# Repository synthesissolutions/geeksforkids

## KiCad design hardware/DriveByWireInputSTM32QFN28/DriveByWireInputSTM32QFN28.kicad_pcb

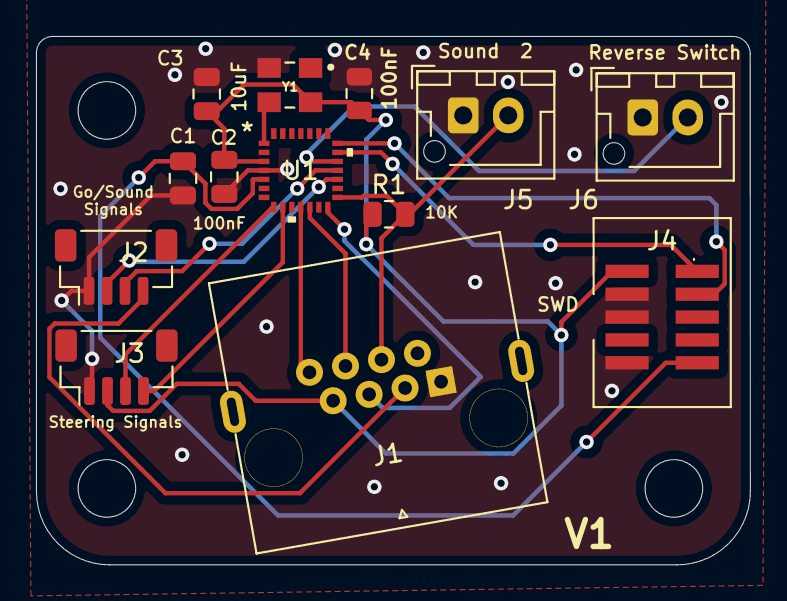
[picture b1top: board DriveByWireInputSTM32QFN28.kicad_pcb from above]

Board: 2 copper layers, 39.7 x 29.4 mm, 16 parts (0 on the bottom side), 16 nets.

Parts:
C1, C2, C4: 100nF; C_0805_2012Metric
C3: 10uF; C_0805_2012Metric
H1, H2, H3: MountingHole; MountingHole_3.2mm_M3
J1: 8P8C; RJ45_x08_Tab_Up
J2, J3: Conn_01x04_Male; JST_SH_BM04B-SRSS-TB_1x04-1MP_P1.00mm_Vertical
J4: Conn_ARM_JTAG_SWD_10; JTAG_SWD_SMD
J5, J6: Conn_01x02_Male; JST_XH_B2B-XH-AM_1x02_P2.50mm_Vertical
R1: 10K; R_0805_2012Metric
U1: STM32G031F4Px; STM32G031G8U6
Y1: ECS-3225MVQ-160-BP-TR; OSC_ECS-3225MVQ-160-BP-TR

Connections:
+3V3: C2.1, C3.1, C4.2, J1.7, J3.2, J4.1 (VTref), R1.1, U1.3 (VDD), Y1.4 (VDD)
/RESET: C1.1, J4.10 (~RESET), U1.5 (PF2-NRST)
AltReverseSwitch: J2.3, U1.18 (PA11PA9)
DriveButton: J2.2, U1.17 (PC6)
GND: C1.2, C2.2, C3.2, C4.1, J1.1, J2.1, J3.1, J4.3 (GND), J4.5 (GND), J4.9 (GNDDetect), J5.1, J6.1, U1.4 (VSS), Y1.2 (GND)
JoyX: J1.5, U1.14 (PB0)
JoyY: J1.6, U1.12 (PA6)
OscillatorIn: U1.1 (PC14-OSC32_IN), Y1.3 (OUTPUT)
Other: J1.8, U1.11 (PA5)
ReverseSwitch: J6.2, U1.19 (PA12PA10)
SWCLK: J4.4 (SWDCLK/TCK), U1.21 (PA14-BOOT0)
SWDIO: J4.2 (SWDIO/TMS), U1.20 (PA13)
SensorCos: J3.4, U1.9 (PA3)
SensorSin: J3.3, U1.8 (PA2)
Sound1: J1.3, J2.4
Sound2: J1.4, J5.2, R1.2, U1.15 (PB1)

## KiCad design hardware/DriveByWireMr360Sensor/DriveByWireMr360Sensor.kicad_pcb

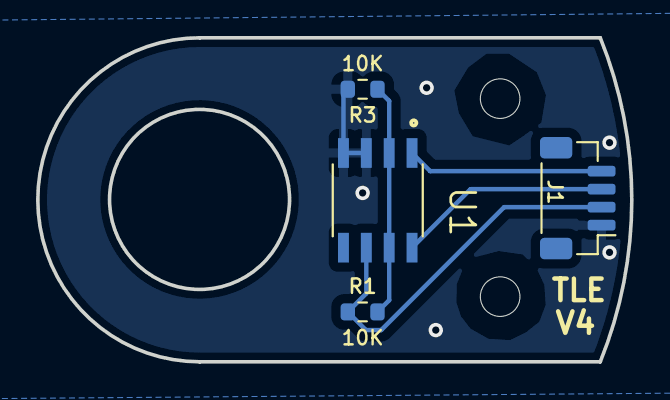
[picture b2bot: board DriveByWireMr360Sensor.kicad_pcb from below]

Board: 2 copper layers, 33.0 x 18.0 mm, 6 parts (4 on the bottom side), 5 nets.

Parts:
H1, H2: MountingHole; MountingHole_2.2mm_M2
J1: Conn_01x04_Male; JST_SH_BM04B-SRSS-TB_1x04-1MP_P1.00mm_Vertical
R1, R3: 10K; R_0603_1608Metric
U1: TLE5501E0001XUMA1; SOIC127P600X175-8N

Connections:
+3V3: J1.2, R1.1, U1.6 (VDD)
AnalogSignal1: J1.3, U1.8 (SIN_P)
AnalogSignal2: J1.4, U1.1 (COS_P)
GND: J1.1, R3.2, U1.3 (GND2), U1.4 (GND1)
unnamed: R1.2, R3.1, U1.2 (COS_N), U1.7 (SIN_N)

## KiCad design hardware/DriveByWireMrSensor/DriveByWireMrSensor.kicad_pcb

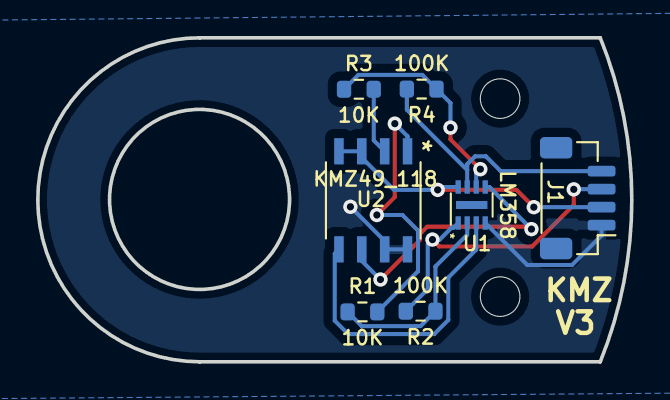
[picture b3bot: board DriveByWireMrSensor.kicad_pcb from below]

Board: 2 copper layers, 33.0 x 18.0 mm, 9 parts (7 on the bottom side), 10 nets.

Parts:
H1, H2: MountingHole; MountingHole_2.2mm_M2
J1: Conn_01x04_Male; JST_SH_BM04B-SRSS-TB_1x04-1MP_P1.00mm_Vertical
R1, R3: 10K; R_0603_1608Metric
R2, R4: 100K; R_0603_1608Metric
U1: LM358; DFN-8-LM358
U2: KMZ49_118

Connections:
+3V3: J1.2, U1.8 (V+), U2.3 (VCC2), U2.4 (VCC1)
AnalogSignal1: J1.3, R2.2, U1.1
AnalogSignal2: J1.4, R4.2, U1.7
GND: J1.1, U1.4 (V-), U2.7 (GND2), U2.8 (GND1)
LM358_InM1: R1.1, R2.1, U1.2 (-)
LM358_InM2: R3.1, R4.1, U1.6 (-)
LM358_InP1: U1.3 (+), U2.5 (OP1)
LM358_InP2: U1.5 (+), U2.6 (OP2)
SourceSignal1: R1.2, U2.1 (ON1)
SourceSignal2: R3.2, U2.2 (ON2)

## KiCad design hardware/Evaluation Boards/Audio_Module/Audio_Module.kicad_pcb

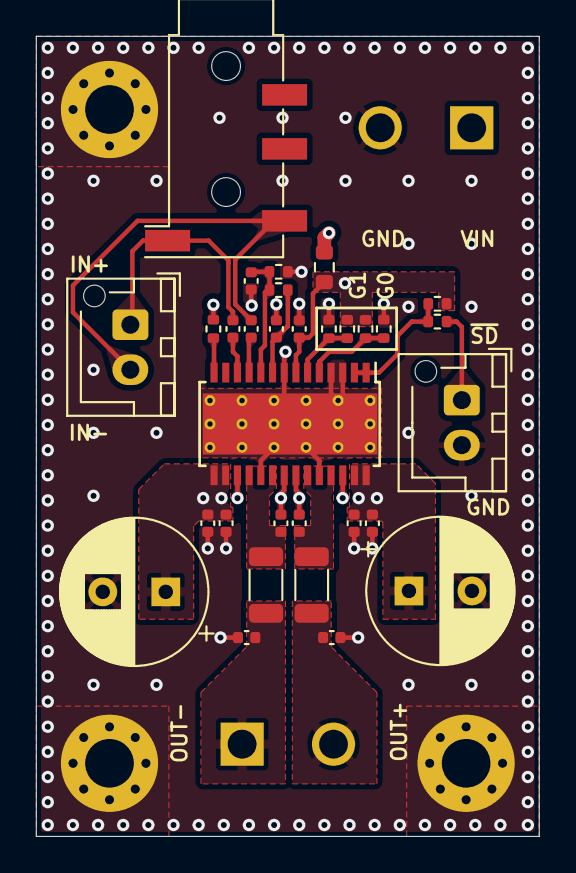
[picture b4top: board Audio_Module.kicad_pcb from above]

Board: 4 copper layers, 27.9 x 44.5 mm, 36 parts (0 on the bottom side), 20 nets.

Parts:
C1, C5: 100uF; CP_Radial_D8.0mm_P3.50mm
C2, C6: 100nF; C_0402_1005Metric
C3, C7, C9, C10: 1nF; C_0402_1005Metric
C4, C14, C15: 1uF; C_0402_1005Metric
C8, C13: 0.47uF; C_0402_1005Metric
C11, C12: 0.68uF; C_0402_1005Metric
FB1, FB2: 120Ohm@100MHz; L_1206_3216Metric
H1, H2, H3: M2.5; MountingHole_2.7mm_M2.5_Pad_Via
J1, J4: 5.08mm; CUI_TB004-508-02BE
J2, J5: 2.54mm; JST_XH_B2B-XH-AM_1x02_P2.50mm_Vertical
J3: 3.5mm; Jack_3.5mm_KoreanHropartsElec_PJ-320D-4A_Horizontal
R1: 10R; R_0603_1608Metric
R2, R3, R4, R5, R10: 100k; R_0402_1005Metric
R6: 1k; R_0402_1005Metric
R7, R8, R9: 0; R_0402_1005Metric
U1: TPA3110D2; HTSSOP-28-1EP_4.4x9.7mm_P0.65mm_EP3.4x9.5mm_Mask2.4x6.17mm_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

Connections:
+12V: C1.1, C2.1, C3.1, C5.1, C6.1, C7.1, J4.1, R1.1, U1.15 (PVCCR), U1.16 (PVCCR), U1.27 (PVCCL), U1.28 (PVCCL)
+12VA: C4.1, R1.2, R2.1, R3.1, R4.1, R5.1, U1.7 (AVCC)
/AUDIO_IN_1_N: C12.1, U1.11 (RINN)
/AUDIO_IN_1_P: C11.2, U1.12 (RINP)
/AUDIO_OUT_FILT_N: C10.2, FB2.2, J1.1
/AUDIO_OUT_FILT_P: C9.1, FB1.2, J1.2
/AUDIO_OUT_N: C13.1, FB2.1, U1.18 (OUTPR), U1.20 (OUTNR)
/AUDIO_OUT_P: C8.1, FB1.1, U1.23 (OUTNL), U1.25 (OUTPL)
/BSN: C13.2, U1.17 (BSPR), U1.21 (BSNR)
/BSP: C8.2, U1.22 (BSNL), U1.26 (BSPL)
/GAIN0: R4.2, R7.1, U1.5 (GAIN0)
/GAIN1: R5.2, R8.1, U1.6 (GAIN1)
/GVDD: C14.1, R9.1, U1.9 (GVDD)
/PBTL: R2.2, U1.14 (PBTL)
/PLIMIT: C15.1, R9.2, R10.1, U1.10 (PLIMIT)
/~SD_2: R3.2, R6.2, U1.1 (~SD), U1.2 (~FAULT)
AUDIO_IN_N: C12.2, J2.2, J3.T
AUDIO_IN_P: C11.1, J2.1, J3.S
GND: C1.2, C2.2, C3.2, C4.2, C5.2, C6.2, C7.2, C9.2, C10.1, C14.2, C15.2, H1.1, H2.1, H3.1, J4.2, J5.2, R7.2, R8.2, R10.2, U1.3 (LINP), U1.4 (LINN), U1.8 (AGND), U1.19 (PGND), U1.24 (PGND), U1.29 (GND)
~SD: J5.1, R6.1

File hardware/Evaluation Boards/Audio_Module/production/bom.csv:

Designator,Footprint,Quantity,Value,LCSC Part #
"C1, C5",CP_Radial_D8.0mm_P3.50mm,2,100uF,C112510
"C10, C3, C7, C9",0402,4,1nF,C106205
"C11, C12",0402,2,0.68uF,C113784
"C13, C8",0402,2,0.47uF,C437527
"C14, C15, C4",0402,3,1uF,C1518208
"C2, C6",0402,2,100nF,C105882
"FB1, FB2",1206,2,120Ohm@100MHz,C3011219
"J2, J5",JST_XH_B2B-XH-AM_1x02_P2.50mm_Vertical,2,2.54mm,C158012
J3,Jack_3.5mm_KoreanHropartsElec_PJ-320D-4A_Horizontal,1,3.5mm,C431535
R1,0603,1,10R,C22859
"R10, R2, R3, R4, R5",0402,5,100k,C60491
R6,0402,1,1k,C11702
"R7, R8, R9",0402,3,0,C17168
U1,HTSSOP-28-1EP_4.4x9.7mm_P0.65mm_EP3.4x9.5mm_Mask2.4x6.17mm_ThermalVias,1,TPA3110D2,C30132

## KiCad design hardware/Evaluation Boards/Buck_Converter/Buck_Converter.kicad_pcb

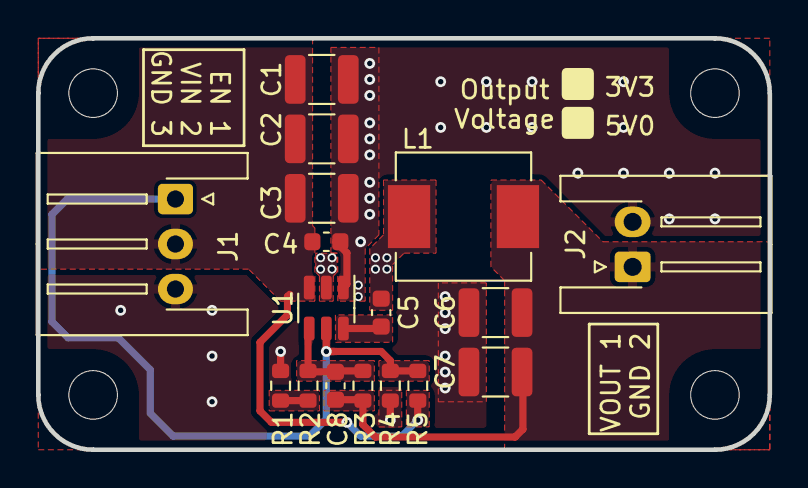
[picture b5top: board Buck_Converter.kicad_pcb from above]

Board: 2 copper layers, 40.6 x 22.9 mm, 21 parts (0 on the bottom side), 8 nets.

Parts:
C1, C2, C3: 10µF; C_1210_3225Metric
C4, C5: 0.1µF; C_0603_1608Metric
C6, C7: 47µF; C_1210_3225Metric
C8: 150pF; C_0603_1608Metric
H1, H2, H3, H4: M2.5; MountingHole_2.7mm_M2.5_ISO14580
J1: Conn_01x03; JST_XH_S3B-XH-A-1_1x03_P2.50mm_Horizontal
J2: Conn_01x02; JST_XH_S2B-XH-A-1_1x02_P2.50mm_Horizontal
L1: 10µH; L_Sunlord_MWSA0603S
R1: 240Ω 1%; R_0603_1608Metric
R2: 13.3kΩ 1%; R_0603_1608Metric
R3: 100kΩ 1%; R_0603_1608Metric
R4: 105kΩ 1%; R_0603_1608Metric
R5: 511kΩ 1%; R_0603_1608Metric
U1: TPS54302; SOT-23-6

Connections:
+5V: C6.1, C7.1, C8.1, J2.1, L1.2, R3.1
+12V: C1.1, C2.1, C3.1, C4.1, J1.2, R5.1, U1.3 (VIN)
/BOOT: C5.1, U1.6 (BOOT)
/EN: J1.1, R4.1, R5.2, U1.5 (EN)
/FB: C8.2, R2.1, R3.2, U1.4 (FB)
/SW: C5.2, L1.1, U1.2 (SW)
GND: C1.2, C2.2, C3.2, C4.2, C6.2, C7.2, J1.3, J2.2, R1.2, R4.2, U1.1 (GND)
unnamed: R1.1, R2.2

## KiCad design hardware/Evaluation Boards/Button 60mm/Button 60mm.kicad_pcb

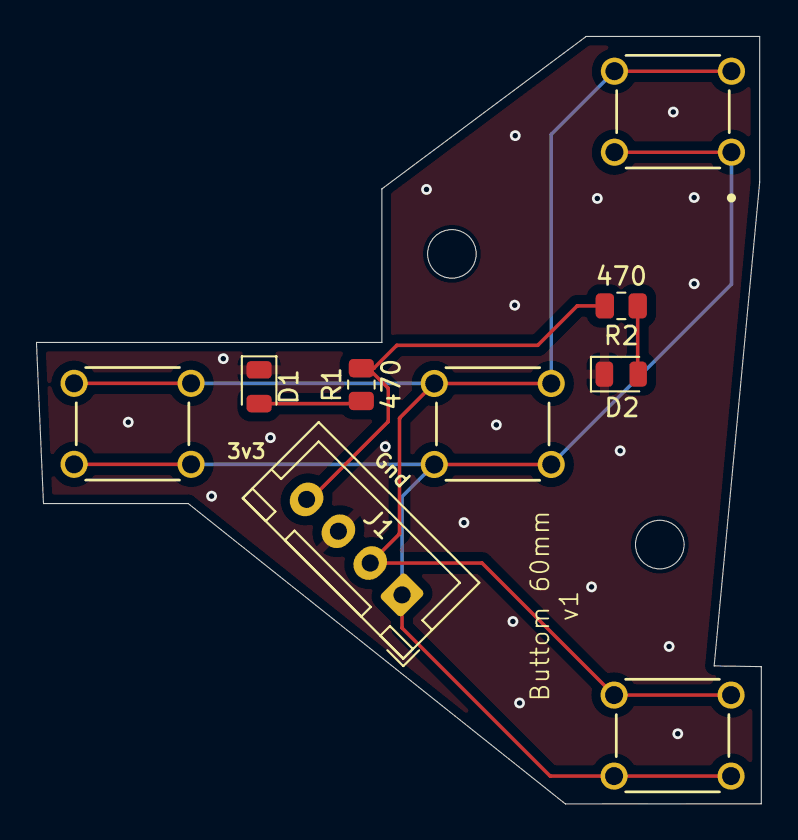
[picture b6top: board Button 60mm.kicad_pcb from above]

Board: 2 copper layers, 40.3 x 42.6 mm, 11 parts (0 on the bottom side), 6 nets.

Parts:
D1, D2: LED_Small; LED_0805_2012Metric
H1, H2: MountingHole; MountingHole_2.7mm_M2.5
J1: Conn_01x04_Pin; JST_XH_B4B-XH-A_1x04_P2.50mm_Vertical
R1, R2: 470; R_0805_2012Metric
SW1, SW2, SW3, SW4: B3F-1050; SW_B3F-1050_OMR

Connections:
+3.3V: J1.4, R1.2, R2.2
BTN_1: J1.1, SW1.1, SW1.2, SW2.1, SW2.2, SW3.1, SW3.2, SW4.1, SW4.2
BTN_2: J1.2, SW1.3, SW1.4, SW2.3, SW2.4, SW3.3, SW3.4, SW4.3, SW4.4
GND: D1.1 (K), D2.1 (K), J1.3
unnamed: D1.2 (A), R1.1
unnamed: D2.2 (A), R2.1

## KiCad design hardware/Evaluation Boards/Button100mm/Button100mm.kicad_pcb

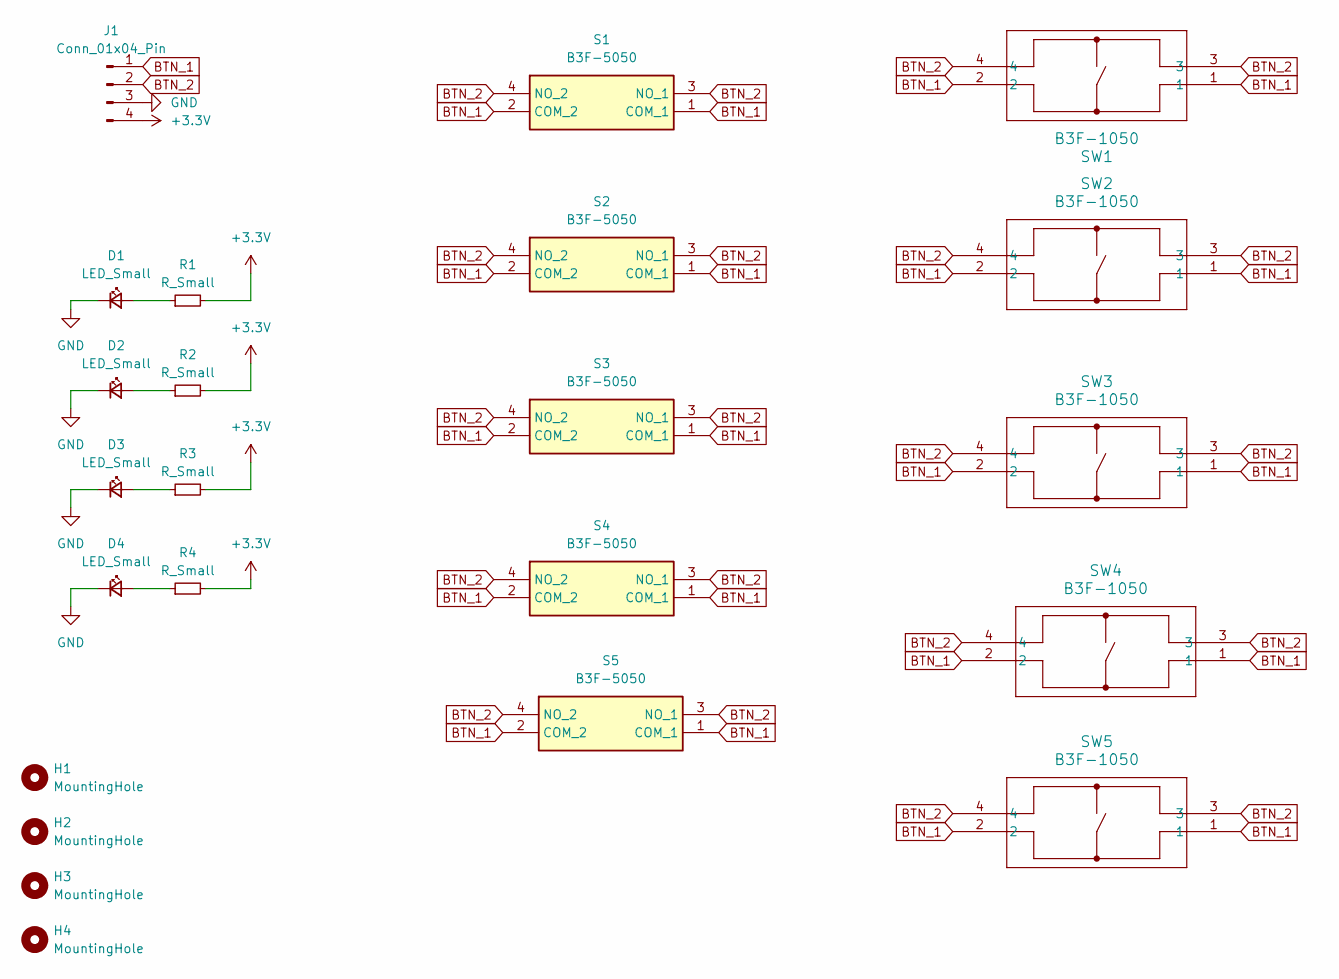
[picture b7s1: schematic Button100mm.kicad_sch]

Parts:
D1, D2, D3, D4: LED_Small; LED_0805_2012Metric
H1, H2, H3, H4: MountingHole; MountingHole_2.7mm_M2.5
J1: Conn_01x04_Pin; JST_XH_B4B-XH-A_1x04_P2.50mm_Vertical
R1, R2, R3, R4: R_Small; R_0805_2012Metric
S1, S2, S3, S4, S5: B3F-5050; B3F-4055; Mouser Part Number 653-B3F-5050
SW1, SW2, SW3, SW4, SW5: B3F-1050; SW_B3F-1050_OMR

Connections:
+3.3V: J1.4, R1.2, R2.2, R3.2, R4.2
BTN_1: J1.1, S1.1 (COM_1), S1.2 (COM_2), S2.1 (COM_1), S2.2 (COM_2), S3.1 (COM_1), S3.2 (COM_2), S4.1 (COM_1), S4.2 (COM_2), S5.1 (COM_1), S5.2 (COM_2), SW1.1, SW1.2, SW2.1, SW2.2, SW3.1, SW3.2, SW4.1, SW4.2, SW5.1, SW5.2
BTN_2: J1.2, S1.3 (NO_1), S1.4 (NO_2), S2.3 (NO_1), S2.4 (NO_2), S3.3 (NO_1), S3.4 (NO_2), S4.3 (NO_1), S4.4 (NO_2), S5.3 (NO_1), S5.4 (NO_2), SW1.3, SW1.4, SW2.3, SW2.4, SW3.3, SW3.4, SW4.3, SW4.4, SW5.3, SW5.4
GND: D1.1 (K), D2.1 (K), D3.1 (K), D4.1 (K), J1.3
unnamed: D1.2 (A), R1.1
unnamed: D2.2 (A), R2.1
unnamed: D3.2 (A), R3.1
unnamed: D4.2 (A), R4.1

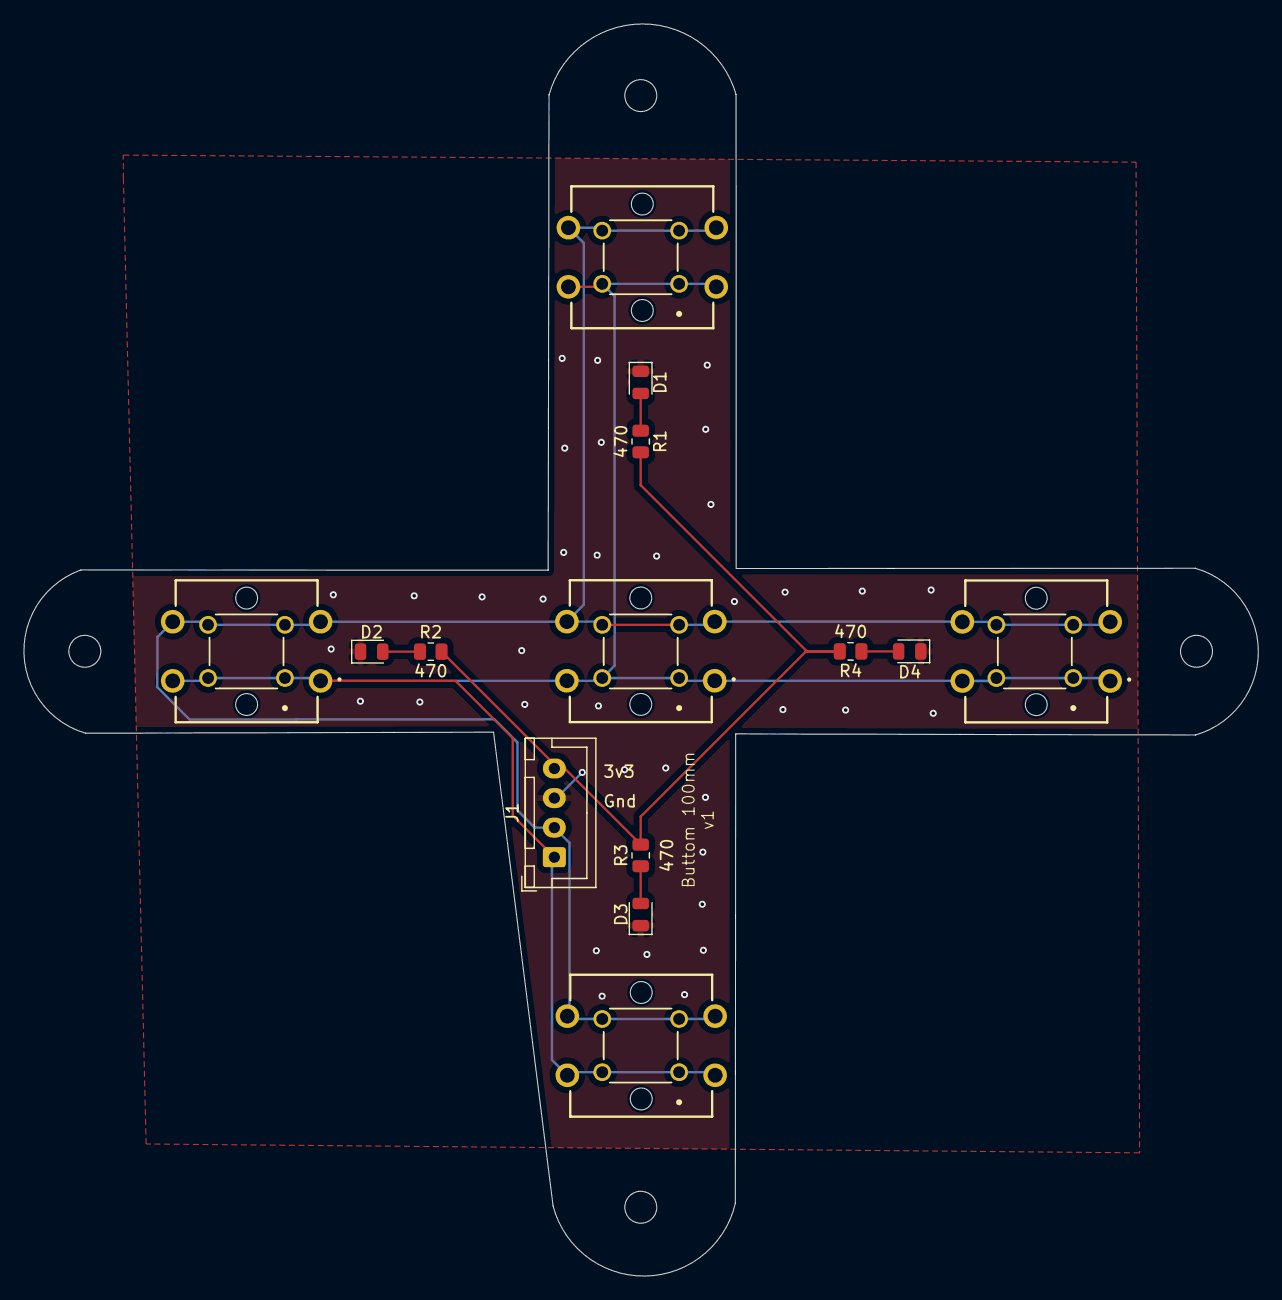
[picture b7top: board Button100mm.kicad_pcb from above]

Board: 2 copper layers, 104.4 x 105.9 mm, 23 parts (0 on the bottom side), 8 nets.

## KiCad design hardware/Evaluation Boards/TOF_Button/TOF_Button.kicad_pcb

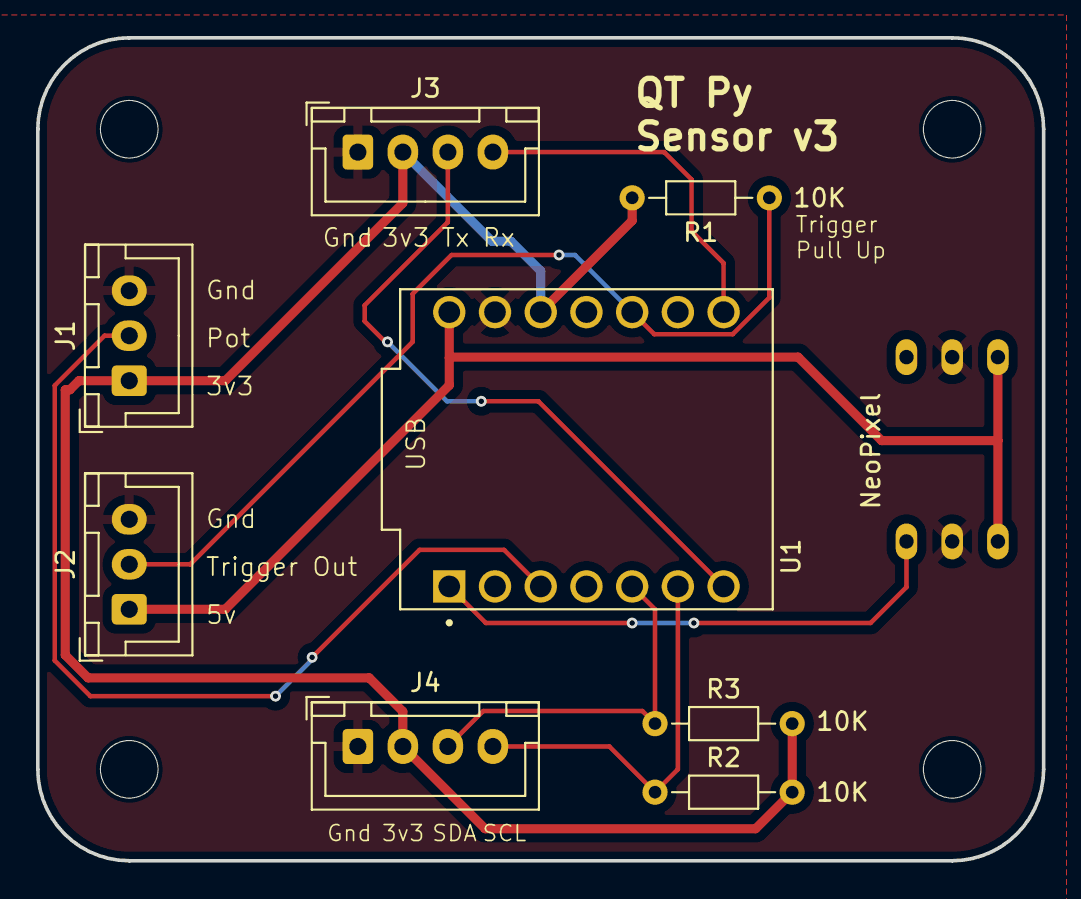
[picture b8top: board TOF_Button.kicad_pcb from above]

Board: 2 copper layers, 55.9 x 45.7 mm, 13 parts (1 on the bottom side), 10 nets.

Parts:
H1, H2, H3, H4: MountingHole; MountingHole_3.2mm_M3
J1: Potentiometer; JST_XH_B3B-XH-A_1x03_P2.50mm_Vertical
J2: Power In Signal Out; JST_XH_B3B-XH-A_1x03_P2.50mm_Vertical
J3, J4: Conn_01x04_Pin; JST_XH_B4B-XH-A_1x04_P2.50mm_Vertical
R1, R2, R3: 10K; R_Axial_DIN0204_L3.6mm_D1.6mm_P7.62mm_Horizontal
U1: ADAFRUIT_QT_PY; MODULE_ADAFRUIT_QT_PY
U2: NeoPixel_Breadboard

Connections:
+3V3: J1.1, J3.2, J4.2, R1.2, R2.2, R3.2, U1.12 (3V3)
+5V: J2.1, U1.14 (5V), U2.1 (5v), U2.6 (5v)
Distance_Pot: J1.2, U1.3 (A2/D2)
GND: J1.3, J2.3, J3.1, J4.1, U1.13 (GND), U2.2 (Gnd), U2.5 (Gnd)
NeoPixel_Data: U1.1 (A0/D0/DAC), U2.3 (DataIn)
RX: J3.4, U1.8 (A7/D7/RX)
SCL: J4.4, R2.1, U1.6 (D5/SCL)
SDA: J4.3, R3.1, U1.5 (D4/SDA)
TX: J3.3, U1.7 (A6/D6/TX)
Trigger_Out: J2.2, R1.1, U1.10 (A9/D9/MISO)

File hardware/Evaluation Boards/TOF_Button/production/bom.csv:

Designator,Footprint,Quantity,Value,LCSC Part #
J1,JST_XH_B3B-XH-A_1x03_P2.50mm_Vertical,1,Potentiometer,
J2,JST_XH_B3B-XH-A_1x03_P2.50mm_Vertical,1,Power In Signal Out,
"J3, J4",JST_XH_B4B-XH-A_1x04_P2.50mm_Vertical,2,Conn_01x04_Pin,
"R1, R2, R3",R_Axial_DIN0204_L3.6mm_D1.6mm_P7.62mm_Horizontal,3,10K,
U1,MODULE_ADAFRUIT_QT_PY,1,ADAFRUIT_QT_PY,
U2,NeoPixel_Breadboard,1,~,

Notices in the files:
parts and their libraries:
Copyright 2021 Accelerated Designs. All rights reserved.
